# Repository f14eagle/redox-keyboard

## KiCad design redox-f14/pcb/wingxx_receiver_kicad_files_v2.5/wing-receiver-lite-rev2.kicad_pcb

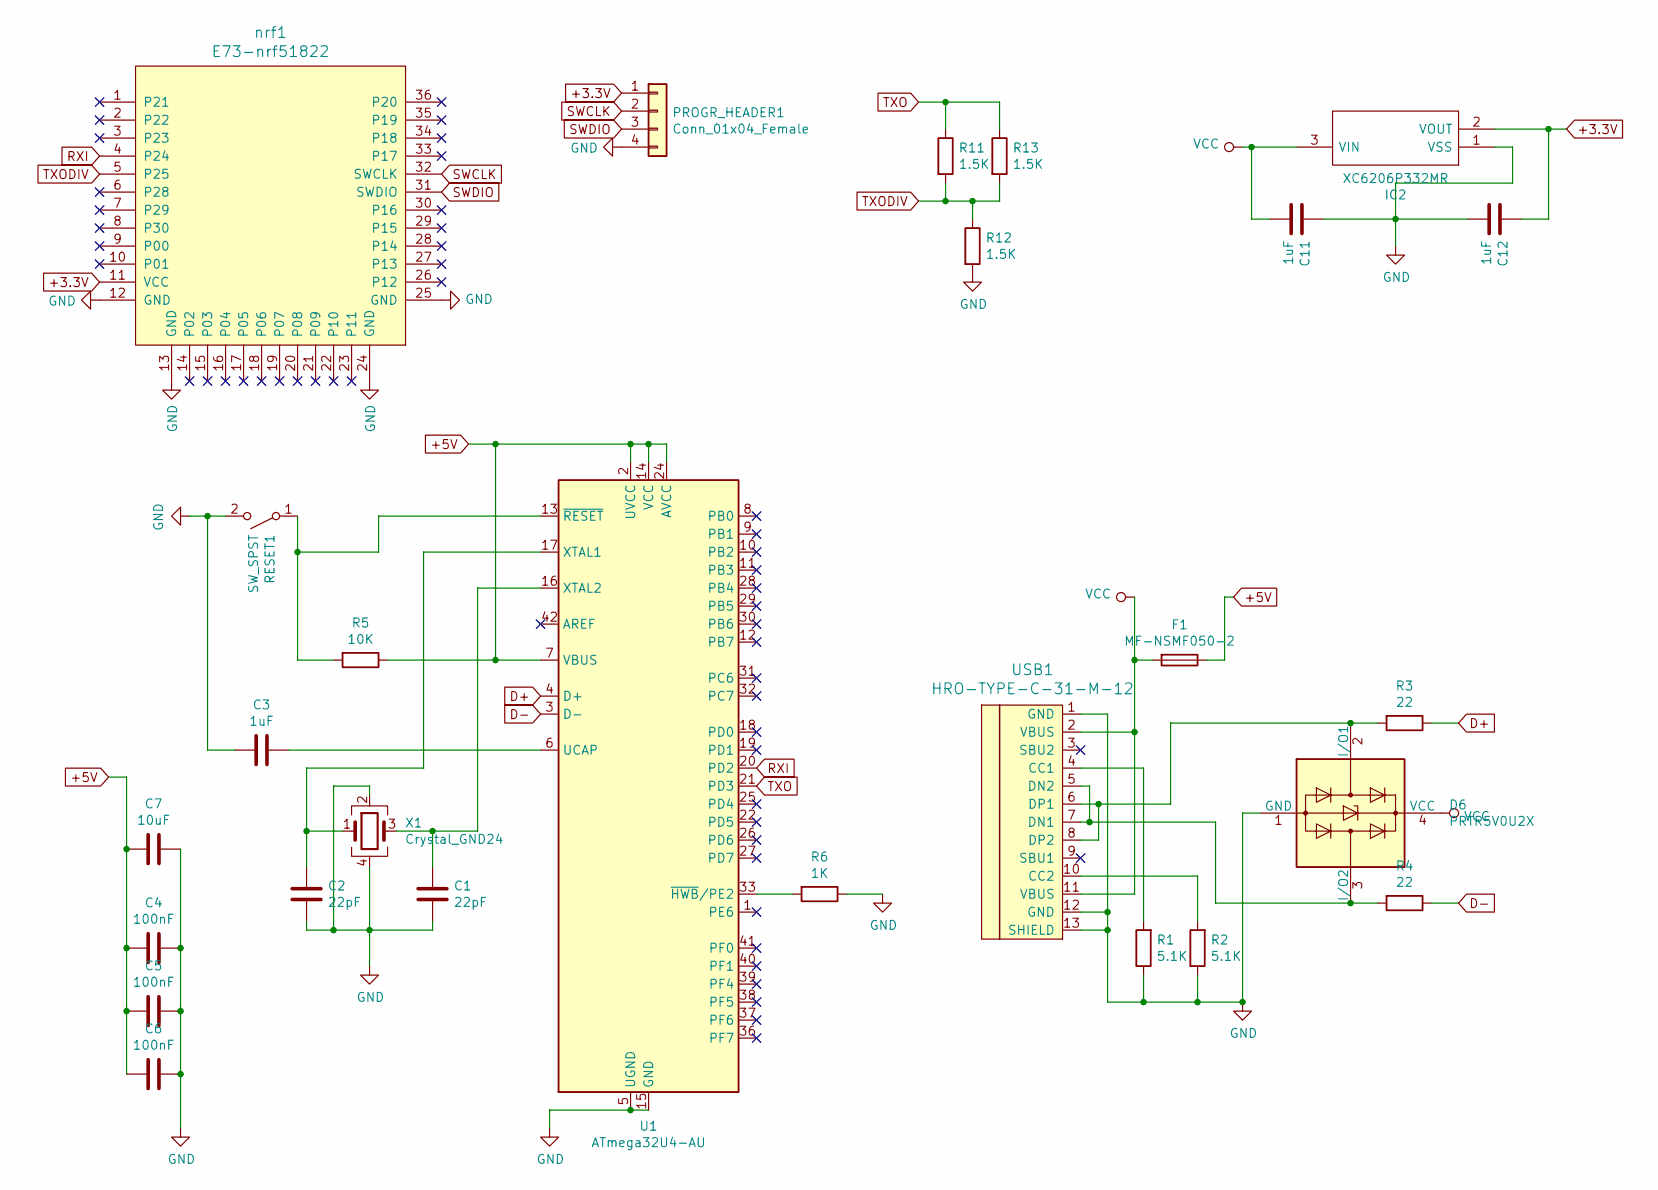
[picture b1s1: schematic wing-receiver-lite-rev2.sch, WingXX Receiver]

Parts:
C1, C2: 22pF; C_0805_2012Metric_Pad1.15x1.40mm_HandSolder
C3, C11, C12: 1uF; C_0805_2012Metric_Pad1.15x1.40mm_HandSolder
C4, C5, C6: 100nF; C_0805_2012Metric_Pad1.15x1.40mm_HandSolder
C7: 10uF; C_0805_2012Metric_Pad1.15x1.40mm_HandSolder
D6: PRTR5V0U2X; SOT-143
F1: MF-NSMF050-2; Fuse_1206_3216Metric_Pad1.42x1.75mm_HandSolder
IC2: XC6206P332MR; SOT95P280X130-3N; Manufacturer_Part_Number XC6206P332MR
PROGR_HEADER1: Conn_01x04_Female; PinHeader_1x04_P2.54mm_Vertical
R1, R2: 5.1K; R_0805_2012Metric_Pad1.15x1.40mm_HandSolder
R3, R4: 22; R_0805_2012Metric_Pad1.15x1.40mm_HandSolder
R5: 10K; R_0805_2012Metric_Pad1.15x1.40mm_HandSolder
R6: 1K; R_0805_2012Metric_Pad1.15x1.40mm_HandSolder
R11, R12, R13: 1.5K; R_0805_2012Metric_Pad1.15x1.40mm_HandSolder
RESET1: SW_SPST; SW_SPST_CK_RS282G05A3
U1: ATmega32U4-AU; TQFP-44_10x10mm_P0.8mm
USB1: HRO-TYPE-C-31-M-12; HRO-TYPE-C-f14
X1: Crystal_GND24; Crystal_SMD_3225-4Pin_3.2x2.5mm_HandSoldering
nrf1: E73-nrf51822; E73-nrf51822-Module

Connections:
+3.3V: C12.1, IC2.2 (VOUT), PROGR_HEADER1.1, nrf1.11 (VCC)
+5V: C4.2, C5.2, C6.2, C7.2, F1.1, R5.1, U1.2 (UVCC), U1.7 (VBUS), U1.14 (VCC), U1.24 (AVCC), U1.34 (VCC), U1.44 (AVCC)
D+: R3.1, U1.4 (D+)
D-: R4.1, U1.3 (D-)
GND: C1.2, C2.2, C3.2, C4.1, C5.1, C6.1, C7.1, C11.1, C12.2, D6.1 (GND), IC2.1 (VSS), PROGR_HEADER1.4, R1.1, R2.1, R6.1, R12.2, RESET1.2 (B), U1.5 (UGND), U1.15 (GND), U1.23 (GND), U1.35 (GND), U1.43 (GND), USB1.1 (GND), USB1.12 (GND), USB1.13 (SHIELD), X1.2, X1.4, nrf1.12 (GND), nrf1.13 (GND), nrf1.24 (GND), nrf1.25 (GND)
unnamed: C1.1, U1.16 (XTAL2), X1.3
unnamed: C2.1, U1.17 (XTAL1), X1.1
unnamed: C3.1, U1.6 (UCAP)
unnamed: D6.2 (I/O1), R3.2, USB1.6 (DP1), USB1.8 (DP2)
unnamed: D6.3 (I/O2), R4.2, USB1.5 (DN2), USB1.7 (DN1)
unnamed: R1.2, USB1.4 (CC1)
unnamed: R2.2, USB1.10 (CC2)
unnamed: R5.2, RESET1.1 (A), U1.13 (~RESET)
unnamed: R6.2, U1.33 (~HWB~/PE2)
RXI: U1.20 (PD2), nrf1.4 (P24)
SWCLK: PROGR_HEADER1.2, nrf1.32 (SWCLK)
SWDIO: PROGR_HEADER1.3, nrf1.31 (SWDIO)
TXO: R11.1, R13.1, U1.21 (PD3)
TXODIV: R11.2, R12.1, R13.2, nrf1.5 (P25)
VCC: C11.2, D6.4 (VCC), F1.2, IC2.3 (VIN), USB1.2 (VBUS), USB1.11 (VBUS)

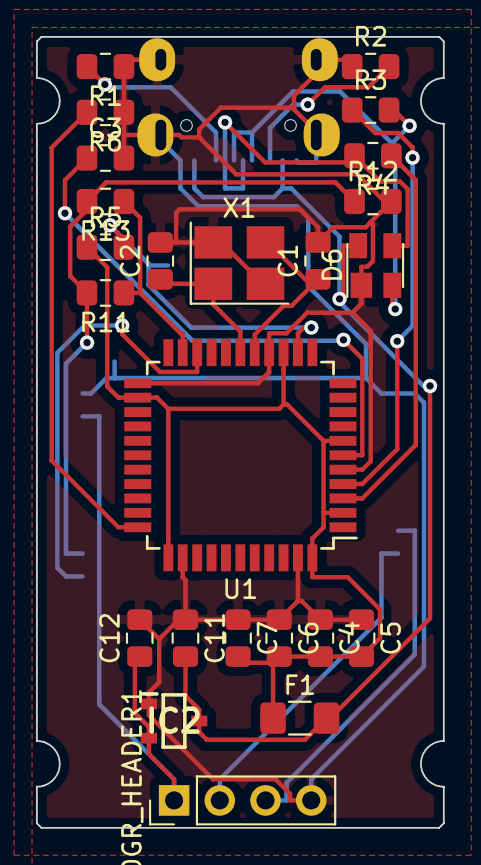
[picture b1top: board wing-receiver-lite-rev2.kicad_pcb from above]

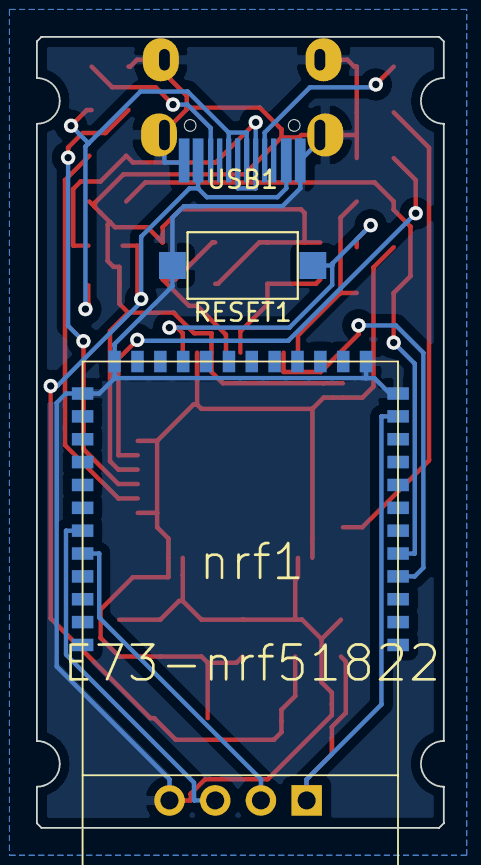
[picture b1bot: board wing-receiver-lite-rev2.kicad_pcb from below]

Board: 2 copper layers, 22.6 x 43.9 mm, 27 parts (3 on the bottom side), 20 nets.

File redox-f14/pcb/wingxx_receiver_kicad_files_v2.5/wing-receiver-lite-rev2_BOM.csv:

Comment,Description,Designator,Footprint,LibRef,Pins,Quantity,±àºÅ
1uF,Desc,"C12,C11,C3,",C_0805_2012Metric_Pad1.15x1.40mm_HandSolder,LibRef,2,3
22pF,Desc,"C2,C1,",C_0805_2012Metric_Pad1.15x1.40mm_HandSolder,LibRef,2,2
100nF,Desc,"C6,C5,C4,",C_0805_2012Metric_Pad1.15x1.40mm_HandSolder,LibRef,2,3
10uF,Desc,"C7,",C_0805_2012Metric_Pad1.15x1.40mm_HandSolder,LibRef,2,1
PRTR5V0U2X,Desc,"D6,",SOT-143,LibRef,4,1
MF-NSMF050-2,Desc,"F1,",Fuse_1206_3216Metric_Pad1.42x1.75mm_HandSolder,LibRef,2,1
XC6206P332MR,Desc,"IC2,",SOT95P280X130-3N,LibRef,3,1
1.5K,Desc,"R13,R12,R11,",R_0805_2012Metric_Pad1.15x1.40mm_HandSolder,LibRef,2,3
5.1K,Desc,"R2,R1,",R_0805_2012Metric_Pad1.15x1.40mm_HandSolder,LibRef,2,2
22,Desc,"R4,R3,",R_0805_2012Metric_Pad1.15x1.40mm_HandSolder,LibRef,2,2
10K,Desc,"R5,",R_0805_2012Metric_Pad1.15x1.40mm_HandSolder,LibRef,2,1
1K,Desc,"R6,",R_0805_2012Metric_Pad1.15x1.40mm_HandSolder,LibRef,2,1
ATmega32U4-AU,Desc,"U1,",TQFP-44_10x10mm_P0.8mm,LibRef,44,1
Crystal_GND24,Desc,"X1,",Crystal_SMD_3225-4Pin_3.2x2.5mm_HandSoldering,LibRef,4,1
SW_SPST,Desc,"RESET1,",SW_SPST_CK_RS282G05A3,LibRef,2,1
E73-nrf51822,Desc,"nrf1,",E73-nrf51822-Module,LibRef,36,1
Through Hole Items 
Conn_01x04_Female,Desc,"PROGR_HEADER1,",PinHeader_1x04_P2.54mm_Vertical,LibRef,4,1
HRO-TYPE-C-31-M-12,Desc,"USB1,",HRO-TYPE-C-f14,LibRef,18,1

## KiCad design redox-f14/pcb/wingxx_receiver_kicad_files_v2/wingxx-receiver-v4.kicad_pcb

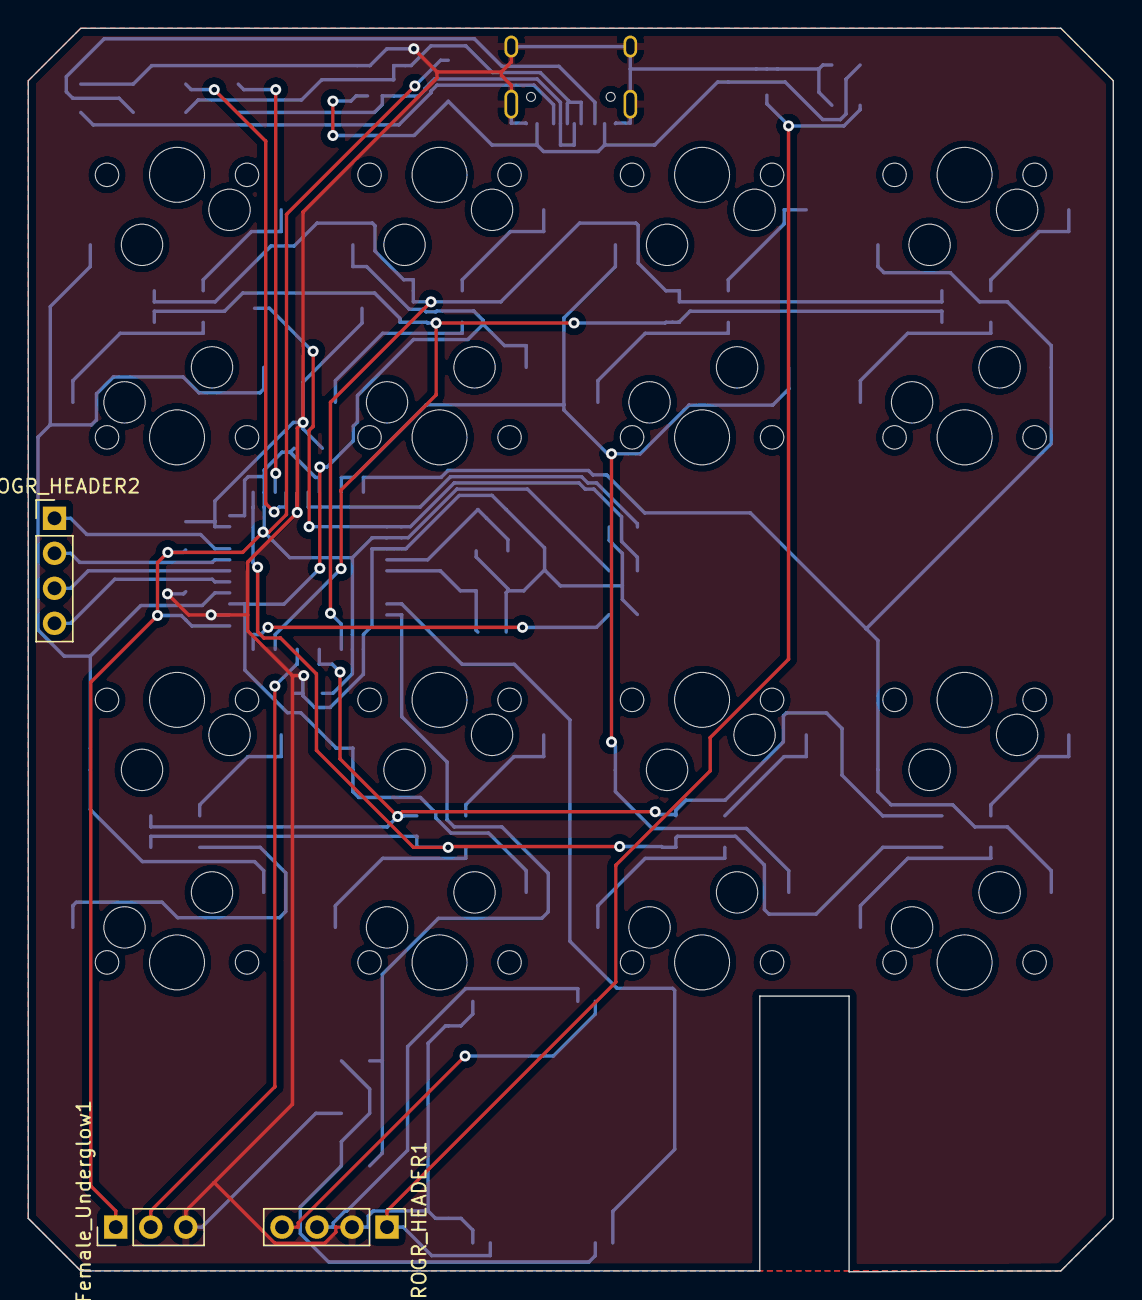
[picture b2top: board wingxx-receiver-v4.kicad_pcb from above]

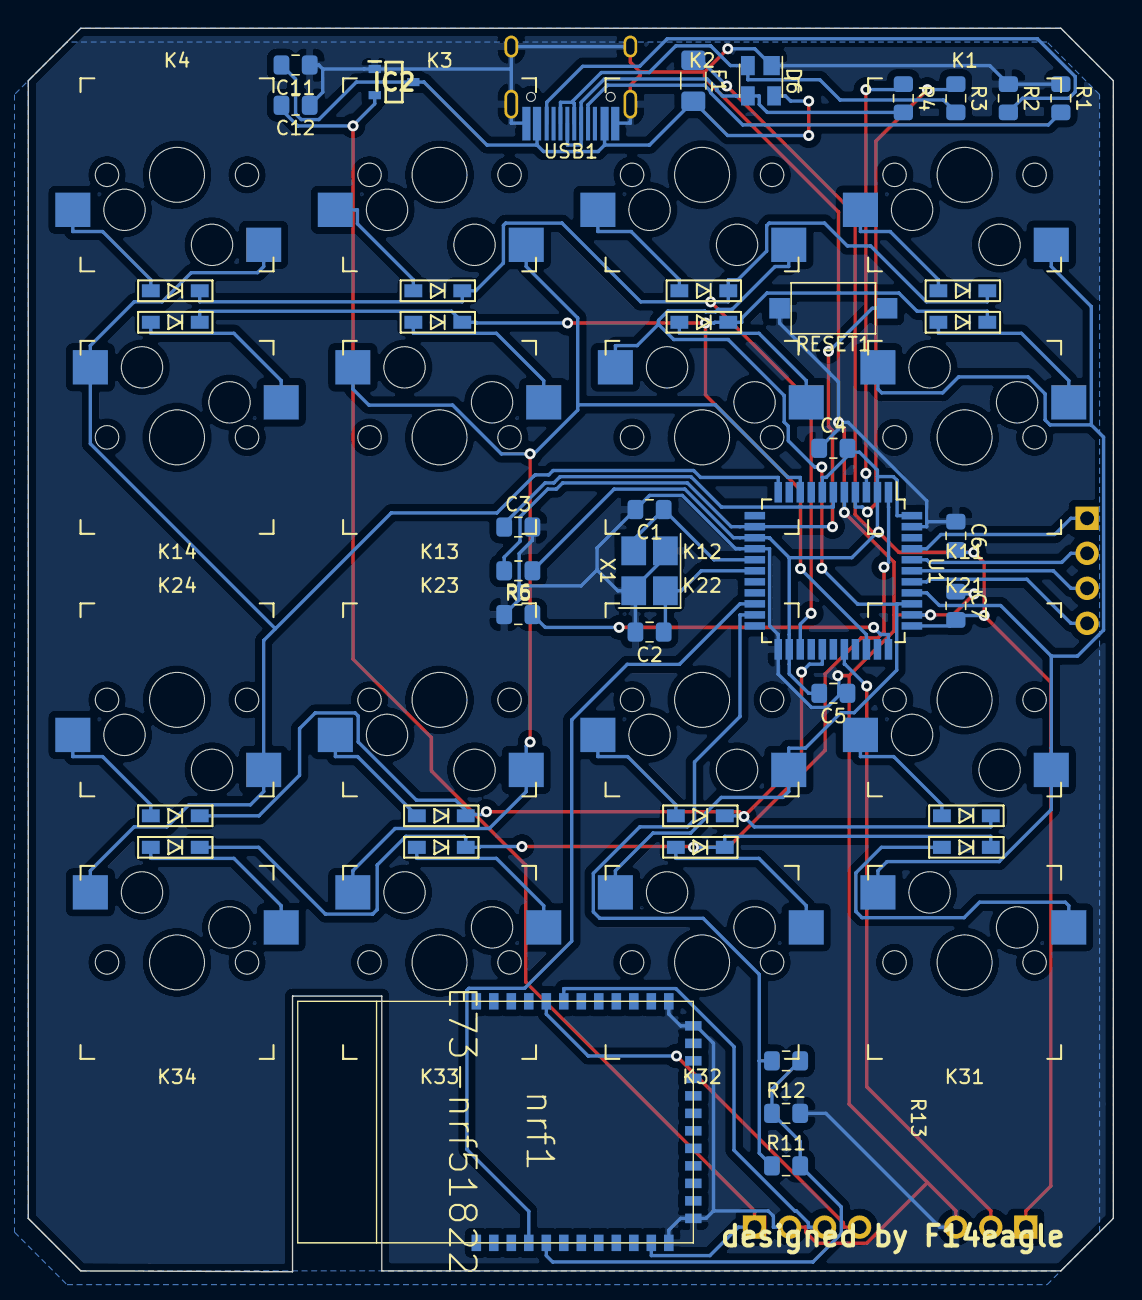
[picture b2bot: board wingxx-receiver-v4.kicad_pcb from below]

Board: 2 copper layers, 78.7 x 90.2 mm, 61 parts (42 on the bottom side), 49 nets.

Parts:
C1, C2: 22pF; C_0805_2012Metric_Pad1.15x1.40mm_HandSolder
C3, C11, C12: 1uF; C_0805_2012Metric_Pad1.15x1.40mm_HandSolder
C4, C5, C6: 100nF; C_0805_2012Metric_Pad1.15x1.40mm_HandSolder
C7: 10uF; C_0805_2012Metric_Pad1.15x1.40mm_HandSolder
ConnFemale_Underglow1: Conn_01x03_Female; PinHeader_1x03_P2.54mm_Vertical
D1, D2, D3, D4, D11, D12, D13, D14, D21, D22, D23, D24, D31, D32, D33, D34: D; D3_SMD_Front
D6: PRTR5V0U2X; SOT-143
F1: MF-NSMF050-2; Fuse_1206_3216Metric_Pad1.42x1.75mm_HandSolder
IC2: XC6206P332MR; SOT95P280X130-3N
K1, K2, K3, K4, K11, K12, K13, K14, K21, K22, K23, K24, K31, K32, K33, K34: KEYSW-redox_rev1-rescue; Kailh_socket
PROGR_HEADER1, PROGR_HEADER2: Conn_01x04_Female; PinHeader_1x04_P2.54mm_Vertical
R1, R2: 5.1K; R_0805_2012Metric_Pad1.15x1.40mm_HandSolder
R3, R4: 22; R_0805_2012Metric_Pad1.15x1.40mm_HandSolder
R5: 10K; R_0805_2012Metric_Pad1.15x1.40mm_HandSolder
R6: 1K; R_0805_2012Metric_Pad1.15x1.40mm_HandSolder
R11, R12, R13: 1.5K; R_0805_2012Metric_Pad1.15x1.40mm_HandSolder
RESET1: SW_SPST; SW_SPST_CK_RS282G05A3
U1: ATmega32U4-AU; TQFP-44_10x10mm_P0.8mm
USB1: HRO-TYPE-C-31-M-12; HRO-TYPE-C-31-M-12-HandSoldering
X1: Crystal_GND24; Crystal_SMD_3225-4Pin_3.2x2.5mm_HandSoldering
nrf1: E73-nrf51822; E73-nrf51822-Module

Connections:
+3.3V: C12.2, IC2.2, PROGR_HEADER1.1, nrf1.11
+5V: C4.2, C5.2, C6.2, C7.2, ConnFemale_Underglow1.1, F1.1, R5.1, U1.2, U1.7, U1.14, U1.24, U1.34, U1.44
D+: R3.1, U1.4
D-: R4.1, U1.3
GND: C1.2, C2.2, C3.2, C4.1, C5.1, C6.1, C7.1, C11.1, C12.1, ConnFemale_Underglow1.3, D6.1, IC2.1, PROGR_HEADER1.2, R1.1, R2.1, R6.1, R12.2, RESET1.2, U1.5, U1.15, U1.23, U1.35, U1.43, USB1.1, USB1.12, USB1.13, X1.2, X1.4, nrf1.12, nrf1.13, nrf1.24, nrf1.25
unnamed: C1.1, U1.16, X1.3
unnamed: C2.1, U1.17, X1.1
unnamed: C3.1, U1.6
unnamed: D1.2, K1.2
unnamed: D2.2, K2.2
unnamed: D3.2, K3.2
unnamed: D4.2, K4.2
unnamed: D6.2, R3.2, USB1.6, USB1.8
unnamed: D6.3, R4.2, USB1.5, USB1.7
unnamed: D11.2, K11.2
unnamed: D12.2, K12.2
unnamed: D13.2, K13.2
unnamed: D14.2, K14.2
unnamed: D21.2, K21.2
unnamed: D22.2, K22.2
unnamed: D23.2, K23.2
unnamed: D24.2, K24.2
unnamed: D31.2, K31.2
unnamed: D32.2, K32.2
unnamed: D33.2, K33.2
unnamed: D34.2, K34.2
unnamed: R1.2, USB1.4
unnamed: R2.2, USB1.10
unnamed: R5.2, RESET1.1, U1.13
unnamed: R6.2, U1.33
POF0: PROGR_HEADER2.1, U1.41
POF1: PROGR_HEADER2.2, U1.40
POF4: PROGR_HEADER2.3, U1.39
POF5: PROGR_HEADER2.4, U1.38
RGB_DATA: ConnFemale_Underglow1.2, U1.29
RXI: U1.20, nrf1.4
SWCLK: PROGR_HEADER1.4, nrf1.32
SWDIO: PROGR_HEADER1.3, nrf1.31
TXO: R11.1, R13.1, U1.21
TXODIV: R11.2, R12.1, R13.2, nrf1.5
VCC: C11.2, D6.4, F1.2, IC2.3, USB1.2, USB1.11
col0: K1.1, K11.1, K21.1, K31.1, U1.37
col1: K2.1, K12.1, K22.1, K32.1, U1.36
col2: K3.1, K13.1, K23.1, K33.1, U1.9
col3: K4.1, K14.1, K24.1, K34.1, U1.11
row0: D1.1, D2.1, D3.1, D4.1, U1.25
row1: D11.1, D12.1, D13.1, D14.1, U1.31
row2: D21.1, D22.1, D23.1, D24.1, U1.27
row3: D31.1, D32.1, D33.1, D34.1, U1.1

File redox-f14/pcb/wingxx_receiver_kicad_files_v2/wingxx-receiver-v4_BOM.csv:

Comment,Description,Designator,Footprint,LibRef,Pins,Quantity,±àºÅ
1uF,Desc,"C12,C11,C3,",C_0805_2012Metric_Pad1.15x1.40mm_HandSolder,LibRef,2,3
22pF,Desc,"C2,C1,",C_0805_2012Metric_Pad1.15x1.40mm_HandSolder,LibRef,2,2
100nF,Desc,"C6,C5,C4,",C_0805_2012Metric_Pad1.15x1.40mm_HandSolder,LibRef,2,3
10uF,Desc,"C7,",C_0805_2012Metric_Pad1.15x1.40mm_HandSolder,LibRef,2,1
D,Desc,"D34,D33,D32,D31,D24,D23,D22,D21,D14,D13,D12,D11,D4,D3,D2,D1,",D3_SMD_Front,LibRef,2,16
PRTR5V0U2X,Desc,"D6,",SOT-143,LibRef,4,1
MF-NSMF050-2,Desc,"F1,",Fuse_1206_3216Metric_Pad1.42x1.75mm_HandSolder,LibRef,2,1
XC6206P332MR,Desc,"IC2,",SOT95P280X130-3N,LibRef,3,1
1.5K,Desc,"R13,R12,R11,",R_0805_2012Metric_Pad1.15x1.40mm_HandSolder,LibRef,2,3
5.1K,Desc,"R2,R1,",R_0805_2012Metric_Pad1.15x1.40mm_HandSolder,LibRef,2,2
22,Desc,"R4,R3,",R_0805_2012Metric_Pad1.15x1.40mm_HandSolder,LibRef,2,2
10K,Desc,"R5,",R_0805_2012Metric_Pad1.15x1.40mm_HandSolder,LibRef,2,1
1K,Desc,"R6,",R_0805_2012Metric_Pad1.15x1.40mm_HandSolder,LibRef,2,1
SW_SPST,Desc,"RESET1,",SW_SPST_CK_RS282G05A3,LibRef,2,1
ATmega32U4-AU,Desc,"U1,",TQFP-44_10x10mm_P0.8mm,LibRef,44,1
Crystal_GND24,Desc,"X1,",Crystal_SMD_3225-4Pin_3.2x2.5mm_HandSoldering,LibRef,4,1
E73-nrf51822,Desc,"nrf1,",E73-nrf51822-Module,LibRef,36,1
Through Hole Items 
Conn_01x03_Female,Desc,"ConnFemale_Underglow1,",PinHeader_1x03_P2.54mm_Vertical,LibRef,3,1
KEYSW-redox_rev1-rescue,Desc,"K34,K33,K32,K31,K24,K23,K22,K21,K14,K13,K12,K11,K4,K3,K2,K1,",Kailh_socket,LibRef,7,16
Conn_01x04_Female,Desc,"PROGR_HEADER2,PROGR_HEADER1,",PinHeader_1x04_P2.54mm_Vertical,LibRef,4,2
HRO-TYPE-C-31-M-12,Desc,"USB1,",HRO-TYPE-C-31-M-12-HandSoldering,LibRef,18,1

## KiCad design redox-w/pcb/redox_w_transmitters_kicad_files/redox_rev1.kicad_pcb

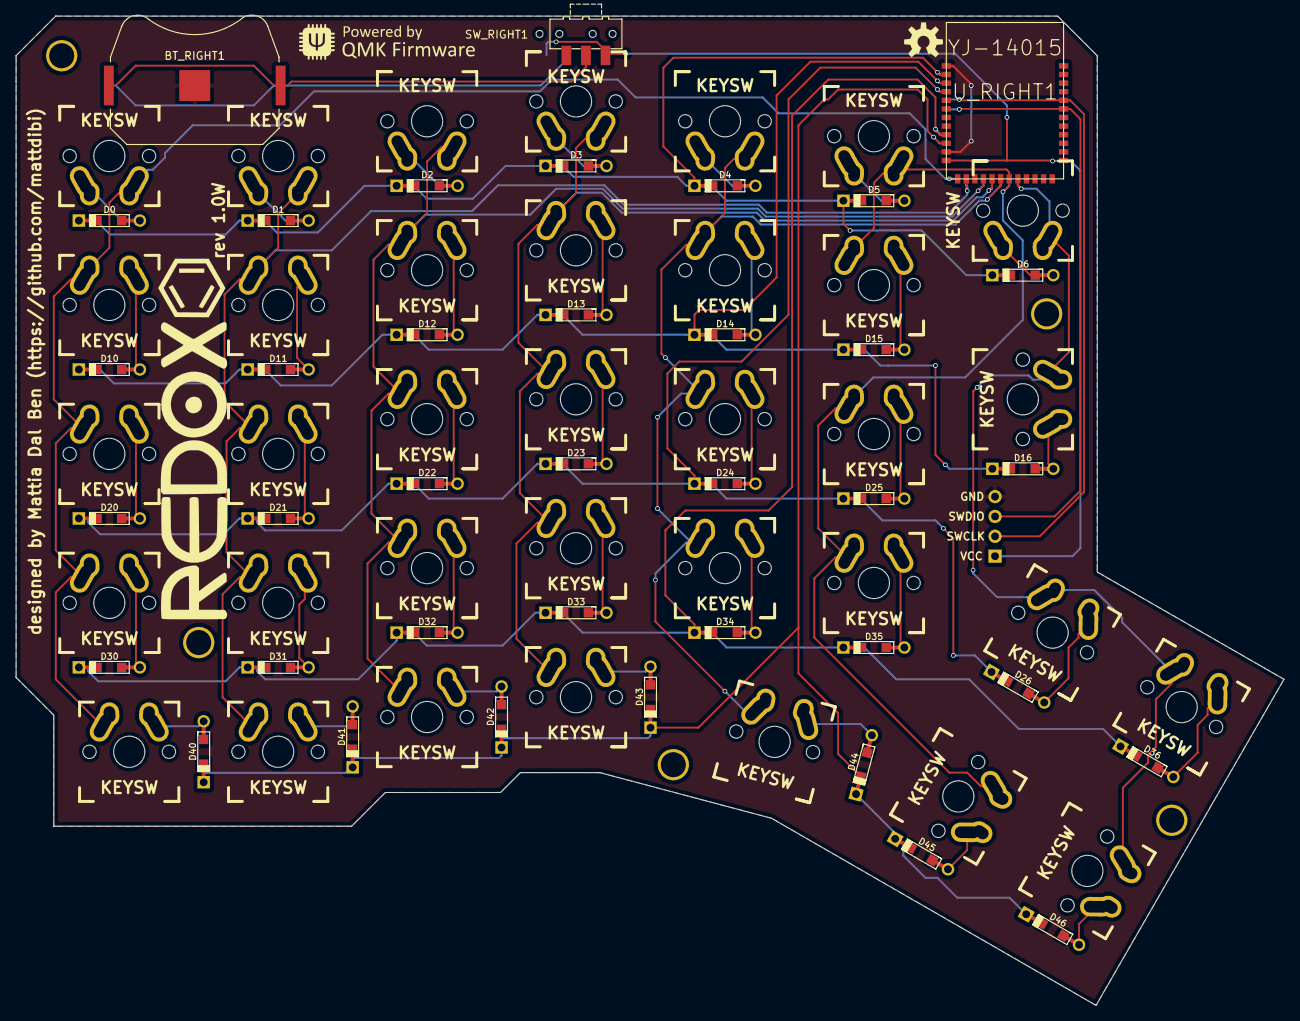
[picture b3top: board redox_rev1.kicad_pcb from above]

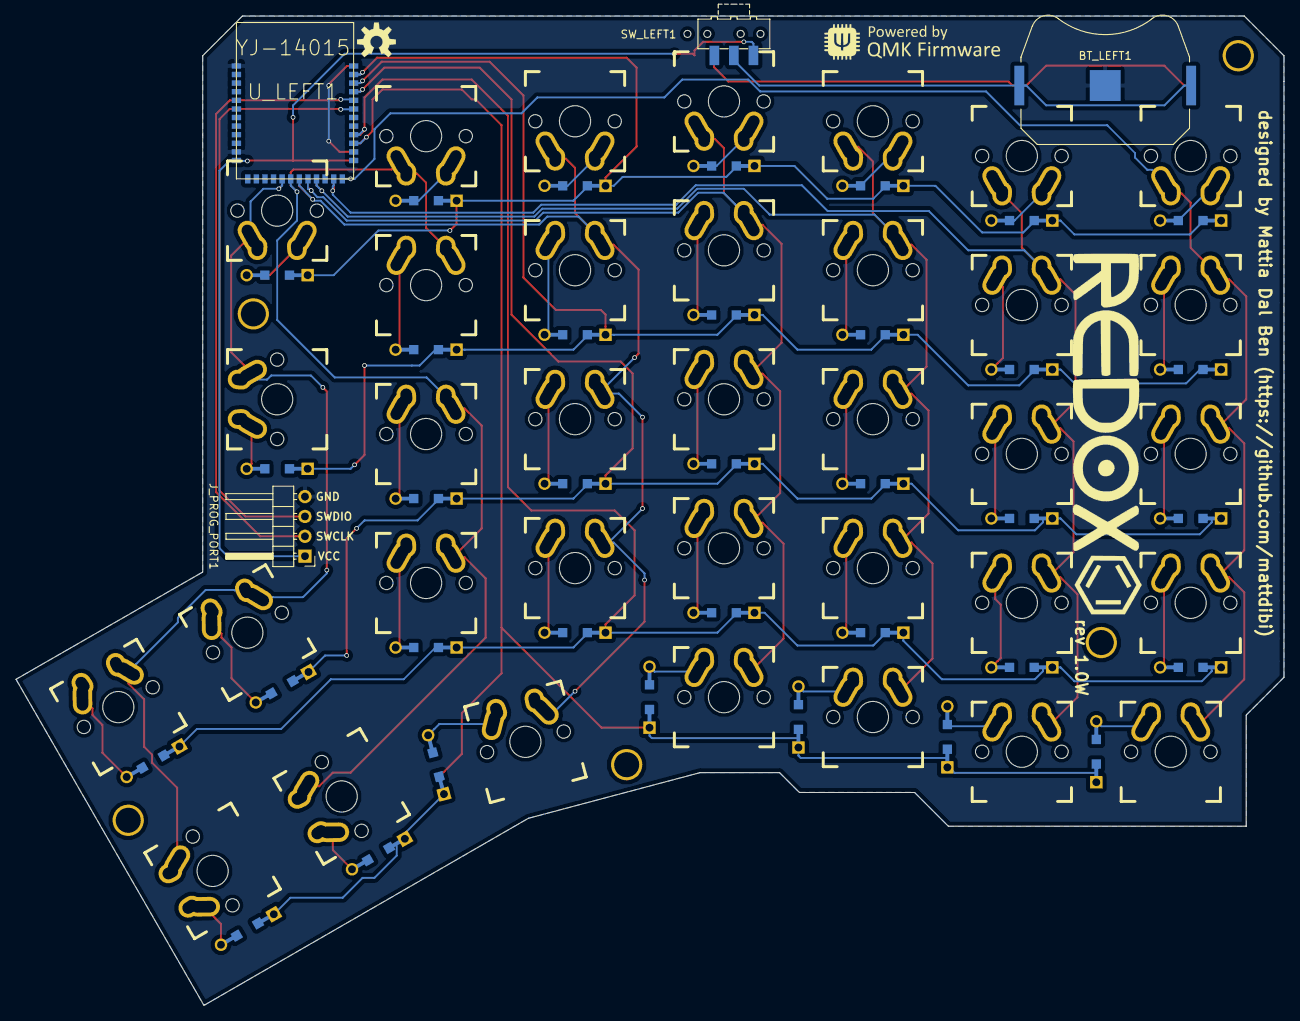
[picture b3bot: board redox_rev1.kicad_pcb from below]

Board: 2 copper layers, 162.2 x 126.5 mm, 82 parts (4 on the bottom side), 53 nets.

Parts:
BT_LEFT1: Battery_Cell; BatteryHolder_Keystone_3034_1x20mm
BT_RIGHT1: Battery_Cell; BatteryHolder_Keystone_3034_1x20mm
D0, D1, D2, D3, D4, D5, D6, D10, D11, D12, D13, D14, D15, D16, D20, D21, D22, D23, D24, D25, D26, D30, D31, D32, D33, D34, D35, D36, D40, D41, D42, D43, D44, D45, D46: D; Diode-dual
HOLE_M3, HOLE_M3#2, HOLE_M3#3, HOLE_M3#4, HOLE_M3#5: VAL**; HOLE_M3
J_PROG_PORT1: Conn_01x04_Male; PinHeader_1x04_P2.54mm_Horizontal
K0, K10, K20, K30, K44: KEYSW; Mx_Alps_125-dualside
K1, K2, K3, K4, K5, K6, K11, K12, K13, K14, K15, K21, K22, K23, K24, K25, K26, K31, K32, K33, K34, K35, K36, K40, K41, K42, K43: KEYSW; Mx_Alps_100-dualside
K16, K45, K46: KEYSW; Mx_Alps_150-dualsided
SW_LEFT1: SW_SPDT; SW_SPDT_CK-JS102011SAQN
SW_RIGHT1: SW_SPDT; SW_SPDT_CK-JS102011SAQN
U_LEFT1: YJ-14015; MY-YJ-14015-Module
U_RIGHT1: YJ-14015; MY-YJ-14015-Module

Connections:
GND: BT_LEFT1.2, BT_RIGHT1.2, J_PROG_PORT1.4, U_LEFT1.1, U_LEFT1.11, U_RIGHT1.1, U_RIGHT1.11
unnamed: BT_LEFT1.1, SW_LEFT1.2
unnamed: BT_RIGHT1.1, SW_RIGHT1.2
unnamed: D0.2, K0.2
unnamed: D1.2, K1.2
unnamed: D2.2, K2.2
unnamed: D3.2, K3.2
unnamed: D4.2, K4.2
unnamed: D5.2, K5.2
unnamed: D6.2, K6.2
unnamed: D10.2, K10.2
unnamed: D11.2, K11.2
unnamed: D12.2, K12.2
unnamed: D13.2, K13.2
unnamed: D14.2, K14.2
unnamed: D15.2, K15.2
unnamed: D16.2, K16.2
unnamed: D20.2, K20.2
unnamed: D21.2, K21.2
unnamed: D22.2, K22.2
unnamed: D23.2, K23.2
unnamed: D24.2, K24.2
unnamed: D25.2, K25.2
unnamed: D26.2, K26.2
unnamed: D30.2, K30.2
unnamed: D31.2, K31.2
unnamed: D32.2, K32.2
unnamed: D33.2, K33.2
unnamed: D34.2, K34.2
unnamed: D35.2, K35.2
unnamed: D36.2, K36.2
unnamed: D40.2, K40.2
unnamed: D41.2, K41.2
unnamed: D42.2, K42.2
unnamed: D43.2, K43.2
unnamed: D44.2, K44.2
unnamed: D45.2, K45.2
unnamed: D46.2, K46.2
SWCLK: J_PROG_PORT1.2, U_LEFT1.32, U_RIGHT1.32
SWDIO: J_PROG_PORT1.3, U_LEFT1.31, U_RIGHT1.31
VCC: J_PROG_PORT1.1, SW_LEFT1.1, SW_RIGHT1.1, U_LEFT1.12, U_RIGHT1.12
col0: K0.1, K10.1, K20.1, K30.1, K40.1, U_LEFT1.24, U_RIGHT1.13
col1: K1.1, K11.1, K21.1, K31.1, K41.1, U_LEFT1.23, U_RIGHT1.14
col2: K2.1, K12.1, K22.1, K32.1, K42.1, U_LEFT1.21, U_RIGHT1.16
col3: K3.1, K13.1, K23.1, K33.1, K43.1, U_LEFT1.20, U_RIGHT1.17
col4: K4.1, K14.1, K24.1, K34.1, K44.1, U_LEFT1.19, U_RIGHT1.18
col5: K5.1, K15.1, K25.1, K35.1, K45.1, U_LEFT1.18, U_RIGHT1.19
col6: K6.1, K16.1, K26.1, K36.1, K46.1, U_LEFT1.17, U_RIGHT1.20
row0: D0.1, D1.1, D2.1, D3.1, D4.1, D5.1, D6.1, U_LEFT1.35, U_RIGHT1.2
row1: D10.1, D11.1, D12.1, D13.1, D14.1, D15.1, D16.1, U_LEFT1.34, U_RIGHT1.3
row2: D20.1, D21.1, D22.1, D23.1, D24.1, D25.1, D26.1, U_LEFT1.33, U_RIGHT1.4
row3: D30.1, D31.1, D32.1, D33.1, D34.1, D35.1, D36.1, U_LEFT1.28, U_RIGHT1.9
row4: D40.1, D41.1, D42.1, D43.1, D44.1, D45.1, D46.1, U_LEFT1.27, U_RIGHT1.10

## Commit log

2019-10-26 update my pcb
2019-10-26 completed rathalos keyboard
2019-10-26 add edge cut
2019-10-27 add case files
2019-11-02 update case v2
2019-12-29 add new receiver
2020-01-07 add wing pad
2020-01-14 update wingxx receiver v2
2020-01-16 update v3 v4 receiver
2020-01-23 add new receiver case v4
2020-02-07 new receiver
2020-03-04 wingxx case update
2020-03-12 update pad case
2020-05-10 update to new style
2020-05-10 add receiver v2.5
2021-04-11 sync to remote
